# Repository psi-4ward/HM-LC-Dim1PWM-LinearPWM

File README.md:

# HM-LC-Dim1PWM-LinearPWM

**HomeMatic Aktor mit linearer PWM Ausgabe über Optokoppler zum Beschalten von PWM-Dim Eingängen.**

Es gibt eine ganze Reihe [Meanwell-Netzteile](https://www.meanwell-web.com/en-gb/led-drivers/all-technology/all-power-format/all-output-voltage-v/all-output-current-a/all-output-power-w/all-input-voltage-v/all-ip-rating/pwm/) mit PWM Eingang zum Dimmen welche über diese Schaltung angesteuert und in Homematic eingebunden werden können.

Es ist darauf zu achten, dass man ein Netzteil mit **3 in 1 dimming** und **dimm-to-off** verwendet:
* 3 in 1: Dimmung über PWM, 0-10V und Potentiometer.
* dimm-to-off: Das Netzteil kann über den DIM-Eingang auch komplett ausgeschaltet werden.

Getestet wurde die Schaltung mit einem Meanwell LCM-40 Netzteil und 30W Konstantstrom-LED-Panel.
Das LCM-40 bietet zusätzlich einen 12V _FAN_ Anschluss worüber den die Schaltung mit Strom versorgt werden kann.

## Hardware

* Arduino Pro Mini 3.3V
* CC1101 Funkmodul
* C1: Elko 2200µF (optional)
* SMD Bauteile Größe 0805
  * C2: Kerko 100nF
  * C3: Kerko 100nF (für L78L05)
  * R1: 1,5kΩ
  * R2, R3: 280Ω
  * R4: 10kΩ
* D1: SMD LED Größe 1206
* SW1: SMD Taster 3x6x2,5mm
* U1: L78L05 Festspannungsregler Größe TO92 (optional)
* U2: Optokoppler PC817
* U3: DS18B20 Temperatursensor (optional)

## Sketch

Ein [Beispiel-Sketch](./HM-LC-Dim1PWM-LinearPWM.ino) ist im Repo hinterlegt.

Interssant ist die Instanziierung der PWM-Class:

```cpp
DimmerControl<HalType,DimmerType,PWM8<200,true,PWM_INVERSE> > control(sdev);
```

Wobei die Parameter des `PWM8`-Templates:
* `steps`: Anzahl Dimmer-Schritte
* `linear`: Flag um eine lineare Dimmerkurve zu erzeugen
* `inverse`: Dimmerkurve invertieren (nötig da Optokoppler)

**Es empfiehlt sich die Brown-Out-Detection des AVR zu deaktivieren um robuster gegen Spannungseinbrüche zu sein.**

## Case:

* [themaddin](https://www.prusaprinters.org/prints/118561-enclosure-for-homematic-diy-dimmer)  

## Changelog

### Version 1.2
* PullUp Widerstand R4 eingefügt 

### Version 1.1
* Markierungen ergänzt

## Lizenz

CreativeCommons BY-NC-SA 4.0

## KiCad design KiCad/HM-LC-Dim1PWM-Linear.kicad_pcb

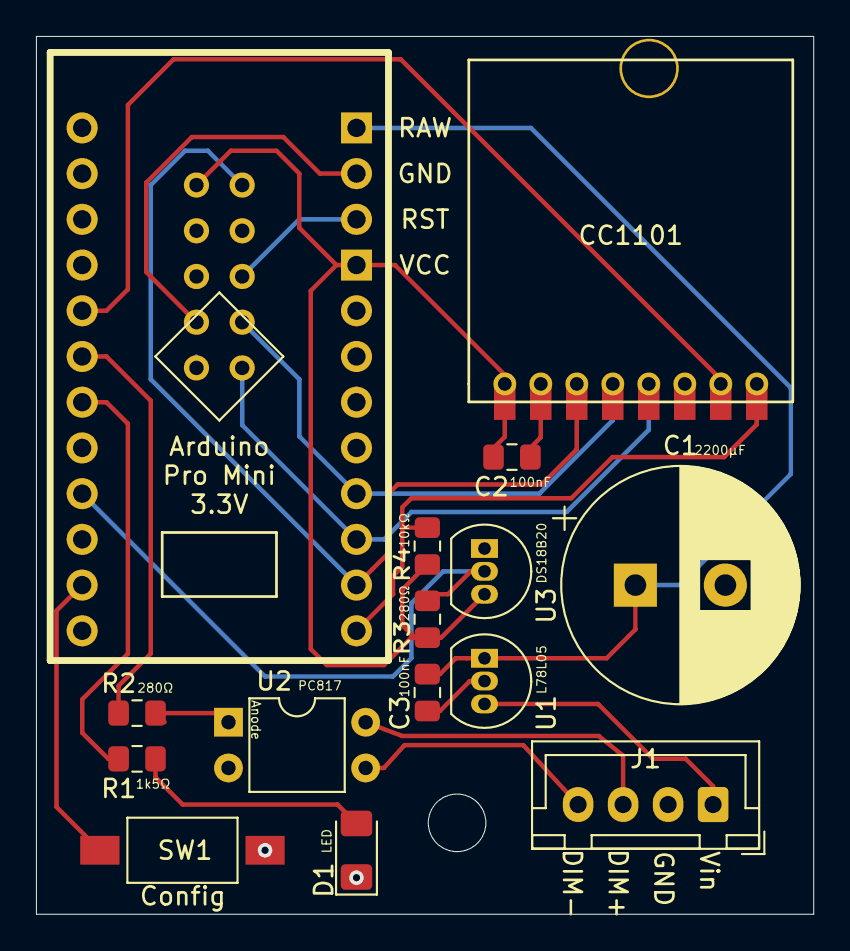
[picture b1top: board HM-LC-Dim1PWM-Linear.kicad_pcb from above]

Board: 2 copper layers, 43.2 x 48.8 mm, 16 parts (1 on the bottom side), 18 nets.

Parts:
B1: ARDUINO_PRO_MINI; Arduino_Pro_Mini_wo_Ax
C1: 2200µF; CP_Radial_D13.0mm_P5.00mm
C2, C3: 100nF; C_0805_2012Metric_Pad1.15x1.40mm_HandSolder
D1: LED; LED_1206_3216Metric_Pad1.42x1.75mm_HandSolder
IC1: CC1101; CC1101_SMD_THT
J1: CONN_04; JST_XH_B4B-XH-A_1x04_P2.50mm_Vertical
J3: AVR-ISP-10; TestPoint_2x5Pads_Pitch2.54mm_Drill0.8mm
R1: 1k5Ω; R_0805_2012Metric_Pad1.15x1.40mm_HandSolder
R2, R3: 280Ω; R_0805_2012Metric_Pad1.15x1.40mm_HandSolder
R4: 10kΩ; R_0805_2012Metric_Pad1.15x1.40mm_HandSolder
SW1: Config; SW_SPST_FSMSM
U1: L78L05_TO92; TO-92_Inline
U2: PC817; DIP-4_W7.62mm
U3: DS18B20; TO-92_Inline

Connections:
1WIRE: B1.9, R3.1, U3.2
/GDO0: B1.5, IC1.7
/PWM: B1.6, R2.1
DIM+: J1.3, U2.4
DIM-: J1.4, U2.3
GND: B1.4, B1.23, C1.2, C2.2, C3.2, D1.1, IC1.2, J1.2, J3.4, J3.6, J3.8, J3.10, SW1.1, U1.2, U2.2, U3.1
unnamed: B1.7, R1.2
unnamed: B1.11, SW1.2
unnamed: B1.13, IC1.8, R4.1
unnamed: B1.14, IC1.3, J3.1
unnamed: B1.15, IC1.5, J3.9
unnamed: B1.16, IC1.4, J3.7
unnamed: B1.22, J3.5
unnamed: B1.24, C1.1, C3.1, U1.1
unnamed: D1.2, R1.1
unnamed: R2.2, U2.1
VCC: B1.21, C2.1, IC1.1, J3.2, R3.2, R4.2, U3.3
Vin: J1.1, U1.3

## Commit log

2020-01-23 init
2020-01-24 Add R4 PullUp for CC1101
2020-02-11 Add image
2020-02-11 Optimized images
2022-01-14 Add Case link
2022-12-03 Don't put avr in sleep mode

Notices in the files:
KiCad/HM-LC-Dim1PWM-Linear.kicad_pcb:
CC BY-NC-SA 4.0
